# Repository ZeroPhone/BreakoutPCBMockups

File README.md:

# BreakoutPCBMockups
Chinese breakout mockups done in KiCad to make 3D models for [ZeroPhone-PCBs](https://github.com/ZeroPhone/ZeroPhone-PCBs) repository (the boards created can be used as base for custom breakouts, too).

## Board photos and dimensions

[DC-DC converter breakout](https://github.com/ZeroPhone/ZeroPhone-PCBs/issues/27)

[TP4056 charger breakout](https://github.com/ZeroPhone/ZeroPhone-PCBs/issues/25)

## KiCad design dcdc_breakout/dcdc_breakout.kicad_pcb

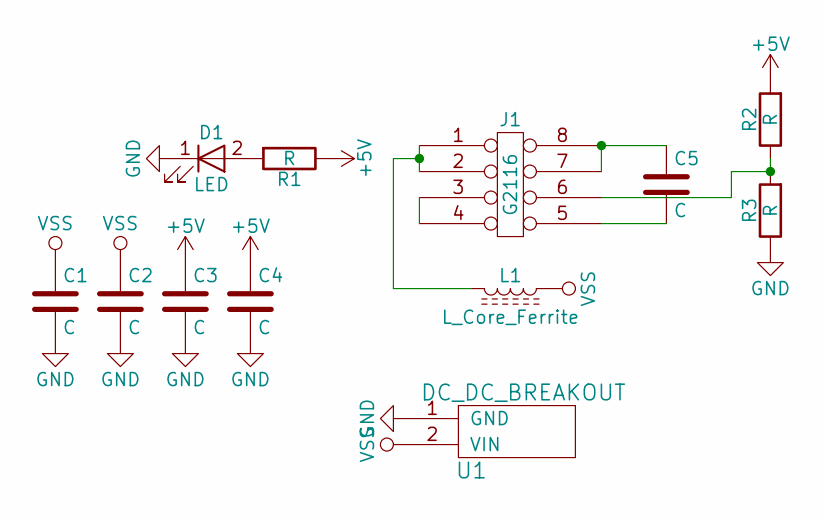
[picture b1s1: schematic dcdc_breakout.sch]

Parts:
C1, C3: C; C_0603
C2, C4: C; C_0805
C5: C; C_1206
D1: LED; LED_0603
J1: G2116; SOIC-8-N
L1: L_Core_Ferrite; INDUCTOR
R1, R2, R3: R; R_0603
U1: DC_DC_BREAKOUT; DC-DC-BREAKOUT

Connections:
+5V: C3.1, C4.1, R1.1, R2.2
GND: C1.2, C2.2, C3.2, C4.2, D1.1 (K), R3.1, U1.1 (GND)
unnamed: C5.1, J1.7, J1.8
unnamed: C5.2, J1.5
unnamed: D1.2 (A), R1.2
unnamed: J1.1, J1.2, L1.2
unnamed: J1.3, J1.4
unnamed: J1.6, R2.1, R3.2
VSS: C1.1, C2.1, L1.1, U1.2 (VIN)

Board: 2 copper layers, 12 parts (0 on the bottom side), 9 nets, no tracks yet.

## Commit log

2017-06-09 Updated gitignore
2017-06-09 DC-DC breakout - dimension check needed
2017-06-09 Adjusted footprints, some more changes
2017-06-09 Initial SIM800 breakout files exported from project
2017-06-09 Initial TP4056 breakout files exported from project
2017-06-09 create inductor shape
2017-06-09 convert inductor to stl
2017-06-09 convert to wrl
    Color the same as the IC on the board RGB=103:103:103
2017-06-09 Place on board
    centered on the pads
2017-06-26 Tweaked the component positioning to match real-life PCB
2017-06-26 Generated 3D files for the breakout
